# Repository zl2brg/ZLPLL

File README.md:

# ZLPLL
Wayne Knowles ZL2BKC ZLPLL ZLPLL-14G Code. Imported v4.2A from his avrstudio project and added open source licences along with Linux Makefile build support.
v4.4A Fixed floating point precision register calculation inaccuracies by moving to 64/32bit integer math. 
Register calculations are based on Andy G4JNT's code. Frequency calculation now accurate to 10Hz below 6.8Ghz and 20Hz above.

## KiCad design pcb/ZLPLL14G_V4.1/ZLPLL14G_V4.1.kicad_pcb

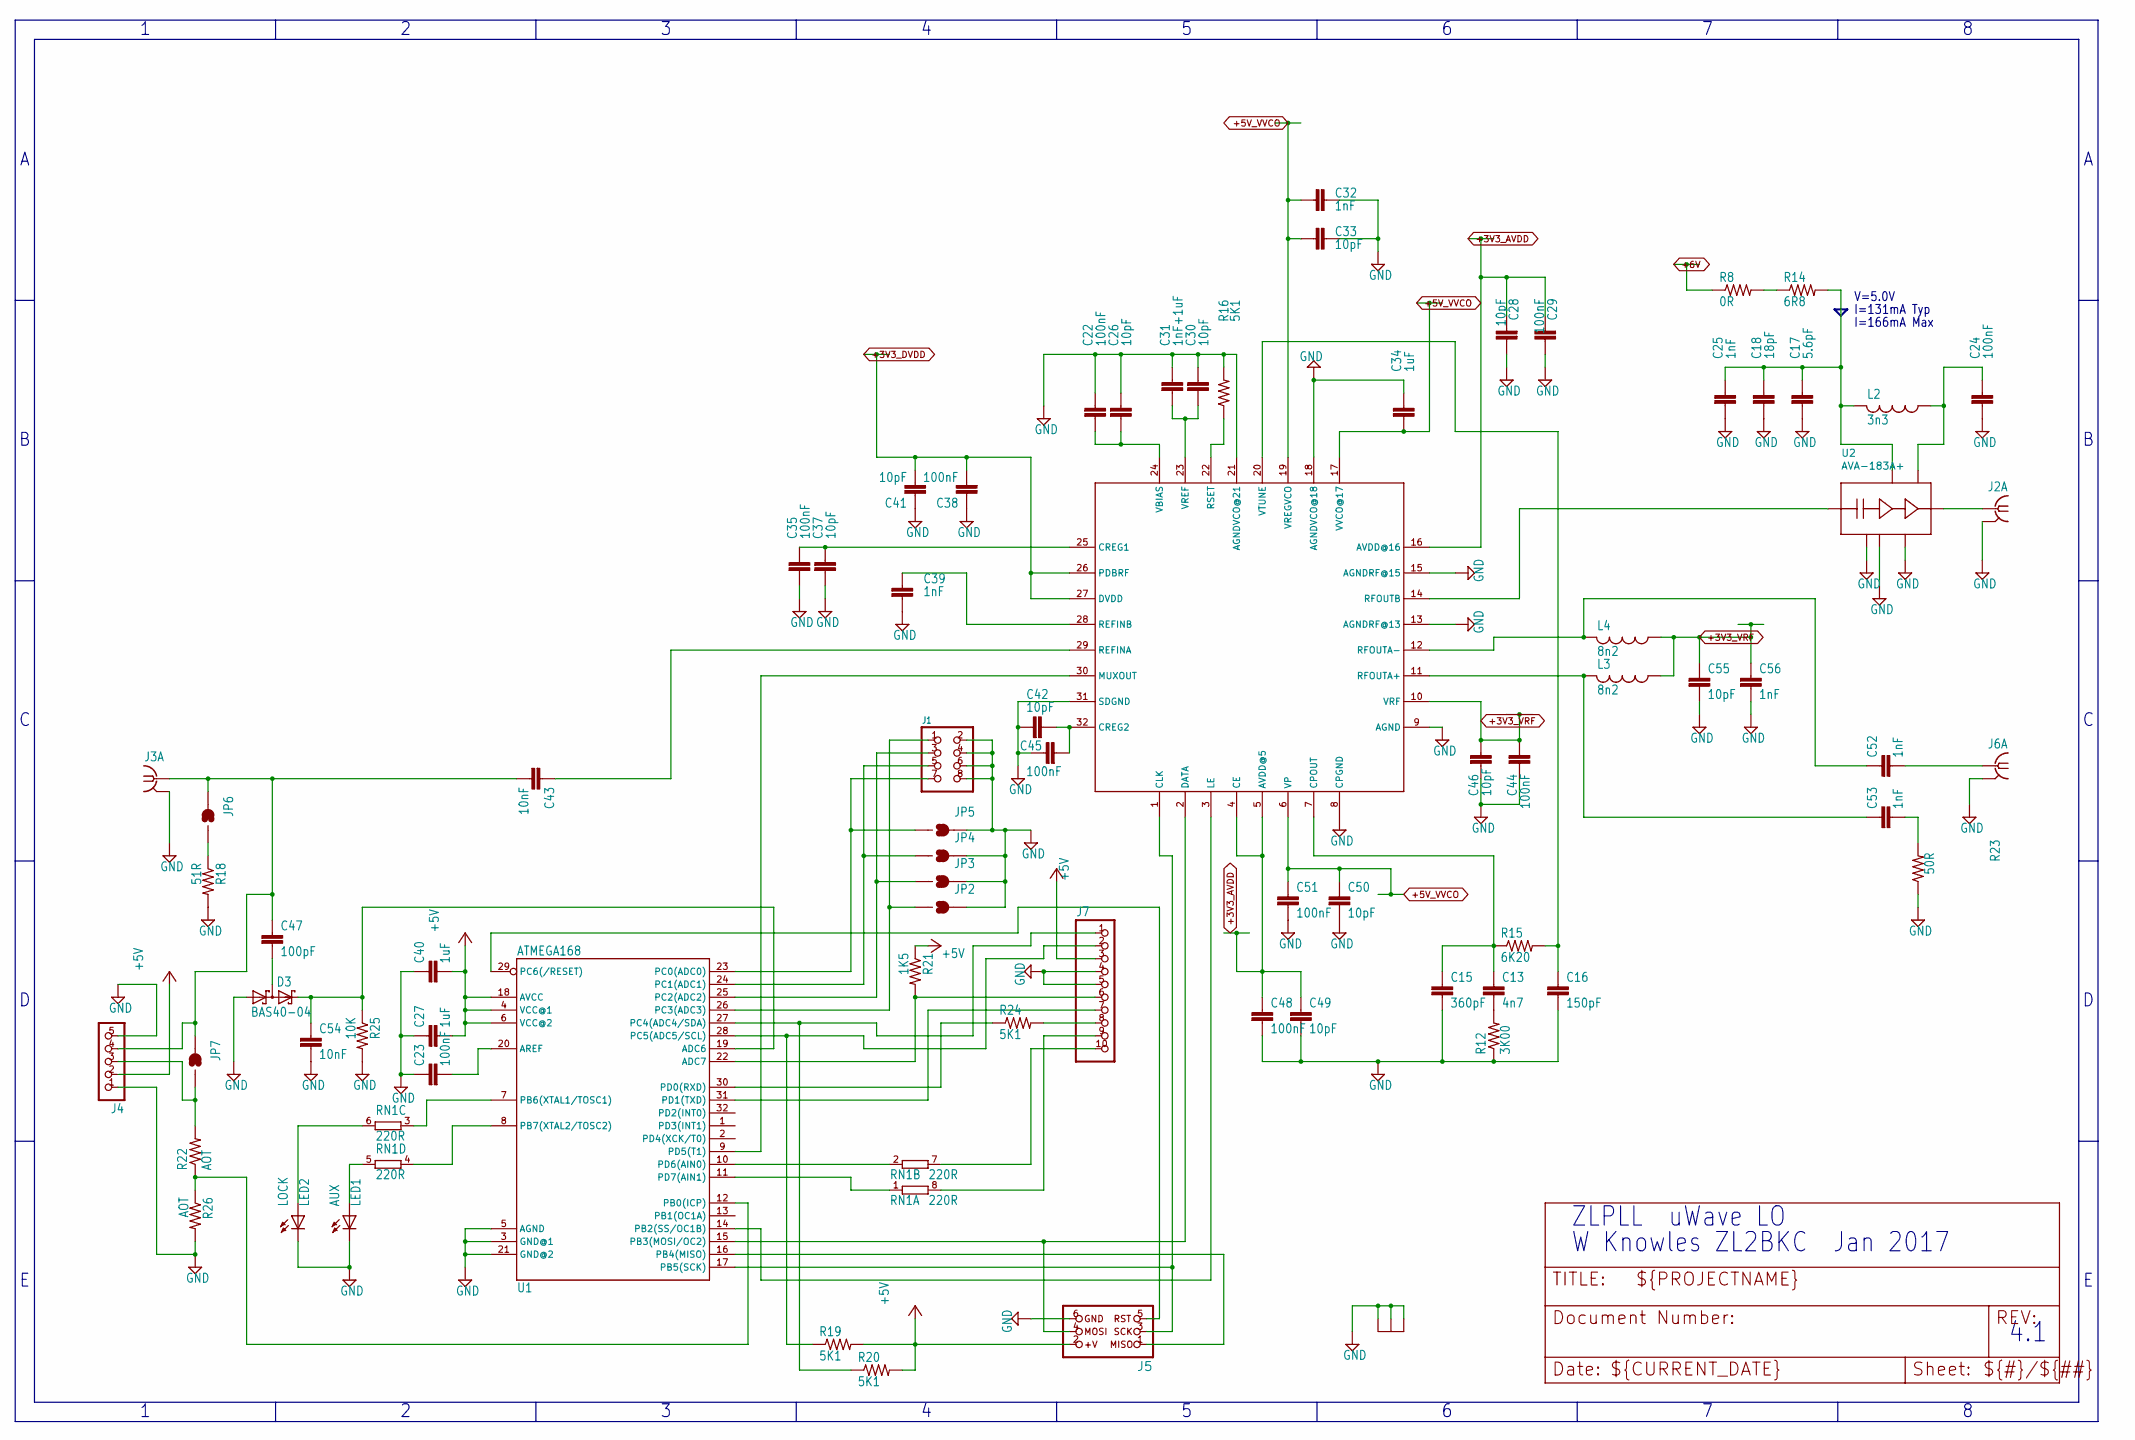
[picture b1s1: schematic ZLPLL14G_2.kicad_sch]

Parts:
C13: 4n7; C0603
C15: 360pF; C0603
C16: 150pF; C0603
C17: 5.6pF; C0402
C18: 18pF; C0402
C22, C24, C29, C35, C38, C44, C45, C48, C51: 100nF; C0402
C23: 100nF; C0603
C25, C32, C39: 1nF; C0402
C26, C28, C30, C33, C37, C41, C42, C46, C49, C50: 10pF; C0402
C27, C40: 1uF; C0603
C31: 1nF+1uF; C0402
C34: 1uF; C0402
C43, C54: 10nF; C0603
C47: 100pF; C0603
C52, C53, C56: 1nF; C0603
C55: 10pF; C0603
D3: BAS40-04; SOT23
J1: CON_HEADER_2X04-PTH; M2X4
J2: SMA-J797
J3, J6: SMA-142-0711-821/826; J502-ND-142-0711-821_826
J4: CON_HEADER_1X05-PTH; M1X5
J5: CON_HEADER_PRG_AVR_ICSP-PTH; HEADER_PRG_2X03
J7: PINHD-1X10; 1X10
JP2, JP3, JP4, JP5, JP7: SOLDERJUMPERNO; SJ_2S-NO
JP6: SOLDERJUMPERNC2; SJ_2S-NOTRACE
L2: 3n3; C0603
L3, L4: 8n2; C0603
LED1: AUX; CHIPLED_0805
LED2: LOCK; CHIPLED_0805
R8: 0R; R1206
R12: 3K00; R0603
R14: 6R8; R1206
R15: 6K20; R0603
R16, R19, R20, R24: 5K1; R0603
R18: 51R; R0603
R21: 1K5; R0603
R22, R26: AOT; R0603
R23: 50R; R0603
R25: 10K; R0603
RN1: 220R; EXBS8V
U1: ATMEGA168; TQFP32-08
U2: AVA-183A+; DQ849
U3: ADF5355; QFN50P500X500X100-33V2N

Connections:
+3V3_AVDD: C28.2, C29.2, C48.1, C49.1, U3.4 (CE), U3.5 (AVDD@5), U3.16 (AVDD@16); also elsewhere on the board
+3V3_DVDD: C38.2, C41.2, U3.26 (PDBRF), U3.27 (DVDD); also elsewhere on the board
+3V3_VRF: C44.1, C46.1, C55.1, C56.1, L3.1, L4.1, U3.10 (VRF); also elsewhere on the board
+5V: C27.2, C40.2, J4.2, J5.2 (+V), J7.3, R19.2, R20.2, R21.1, U1.4 (VCC@1), U1.6 (VCC@2), U1.18 (AVCC); also elsewhere on the board
+5V_VVCO: C32.2, C33.2, C34.2, C50.1, C51.1, U3.6 (VP), U3.17 (VVCO@17), U3.19 (VREGVCO); also elsewhere on the board
+6V: R8.1; also elsewhere on the board
GND: C15.2, C16.2, C17.2, C18.2, C22.1, C23.1, C24.2, C25.2, C26.1, C27.1, C28.1, C29.1, C30.1, C31.1, C32.1, C33.1, C34.1, C35.2, C37.2, C38.1, C39.2, C40.1, C41.1, C42.1, C44.2, C45.1, C46.2, C48.2, C49.2, C50.2, C51.2, C54.2, C55.2, C56.2, D3.1 (A1), J1.2, J1.4, J1.6, J1.8, J2.GND@1 (GND), J2.GND@2 (GND@1), J2.GND@3 (GND@2), J2.GND@4 (GND@3), J2.GND@5 (GND@1), J2.GND@6 (GND@2), J2.GND@7 (GND@3), J3.G@1 (GND), J3.G@2 (GND@1), J3.G@3 (GND@2), J3.G@4 (GND@3), J4.1, J4.5, J5.6 (GND), J6.G@1 (GND), J6.G@2 (GND@1), J6.G@3 (GND@2), J6.G@4 (GND@3), J7.4, J7.5, JP2.2, JP3.2, JP4.2, JP5.2, LED1.C, LED2.C, R12.1, R16.2, R18.2, R23.1, R25.2, R26.2, U1.3 (GND@1), U1.5 (AGND), U1.21 (GND@2), U2.1 (GND@1), U2.6 (GND@2), U2.PAD (GND), U3.8 (CPGND), U3.9 (AGND), U3.13 (AGNDRF@13), U3.15 (AGNDRF@15), U3.18 (AGNDVCO@18), U3.21 (AGNDVCO@21), U3.31 (SDGND), U3.PAD@1_1 (GND@1), U3.PAD@1_2 (GND@2), U3.PAD@1_3 (GND@3), U3.PAD@2_1 (GND@1), U3.PAD@2_2 (GND@2), U3.PAD@2_3 (GND@3), U3.PAD@3_1 (GND@1), U3.PAD@3_2 (GND@2), U3.PAD@3_3 (GND@3); also elsewhere on the board
unnamed: U1.14 (PB2(SS/OC1B)), U3.3 (LE)
unnamed: C23.2, U1.20 (AREF)
unnamed: J5.5 (RST), U1.29 (PC6(/RESET))
unnamed: R16.1, U3.22 (RSET)
unnamed: J7.8, R24.2
unnamed: J7.7, U1.31 (PD1(TXD))
unnamed: R24.1, U1.30 (PD0(RXD))
unnamed: C52.1, L4.2, U3.12 (RFOUTA-)
unnamed: C43.1, U3.29 (REFINA)
unnamed: C47.2, D3.3 (C1A2)
unnamed: C54.1, D3.2 (C2), R25.1, U1.19 (ADC6)
unnamed: C53.1, L3.2, U3.11 (RFOUTA+)
unnamed: J5.4 (MOSI), U1.15 (PB3(MOSI/OC2)), U3.2 (DATA)
unnamed: C13.2, R12.2
unnamed: J2.PIN (1), U2.5 (OUT)
unnamed: C13.1, C15.1, R15.1, U3.7 (CPOUT)
unnamed: U1.9 (PD5(T1)), U3.30 (MUXOUT)
unnamed: RN1.4 (1), U1.8 (PB7(XTAL2/TOSC2))
unnamed: J5.1 (MISO), U1.16 (PB4(MISO))
unnamed: RN1.2 (1), U1.10 (PD6(AIN0))
unnamed: J5.3 (SCK), U1.17 (PB5(SCK)), U3.1 (CLK)
unnamed: C16.1, R15.2, U3.20 (VTUNE)
unnamed: U2.2 (IN), U3.14 (RFOUTB)
unnamed: JP6.1, R18.1
unnamed: C53.2, R23.2
unnamed: J1.7, JP5.1, U1.23 (PC0(ADC0))
unnamed: C24.1, L2.1, U2.8 (DC8)
unnamed: J7.6, R21.2, U1.22 (ADC7)
unnamed: C22.2, C26.2, U3.24 (VBIAS)
unnamed: C30.2, C31.2, U3.23 (VREF)
unnamed: C52.2, J6.1
unnamed: R8.2, R14.1
unnamed: J4.3, JP7.1, R22.2
unnamed: R22.1, R26.1, U1.12 (PB0(ICP))
unnamed: J1.5, JP4.1, U1.24 (PC1(ADC1))
unnamed: J1.3, JP3.1, U1.25 (PC2(ADC2))
unnamed: J1.1, JP2.1, U1.26 (PC3(ADC3))
unnamed: J7.1, R20.1, U1.27 (PC4(ADC4/SDA))
unnamed: J7.2, R19.1, U1.28 (PC5(ADC5/SCL))
unnamed: C43.2, C47.1, J3.1, J4.4, JP6.2, JP7.2
unnamed: RN1.3 (1), U1.7 (PB6(XTAL1/TOSC1))
unnamed: RN1.1, U1.11 (PD7(AIN1))
unnamed: LED1.A, RN1.5 (2)
unnamed: LED2.A, RN1.6 (2)
unnamed: J7.9, RN1.8 (2)
unnamed: J7.10, RN1.7 (2)
unnamed: C17.1, C18.1, C25.1, L2.2, R14.2, U2.7 (DC7)
unnamed: C35.1, C37.1, U3.25 (CREG1)
unnamed: C39.1, U3.28 (REFINB)
unnamed: C42.2, C45.2, U3.32 (CREG2)

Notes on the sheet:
I=166mA Max
V=5.0V
ZLPLL uWave LO
I=131mA Typ
W Knowles ZL2BKC Jan 2017
4.1

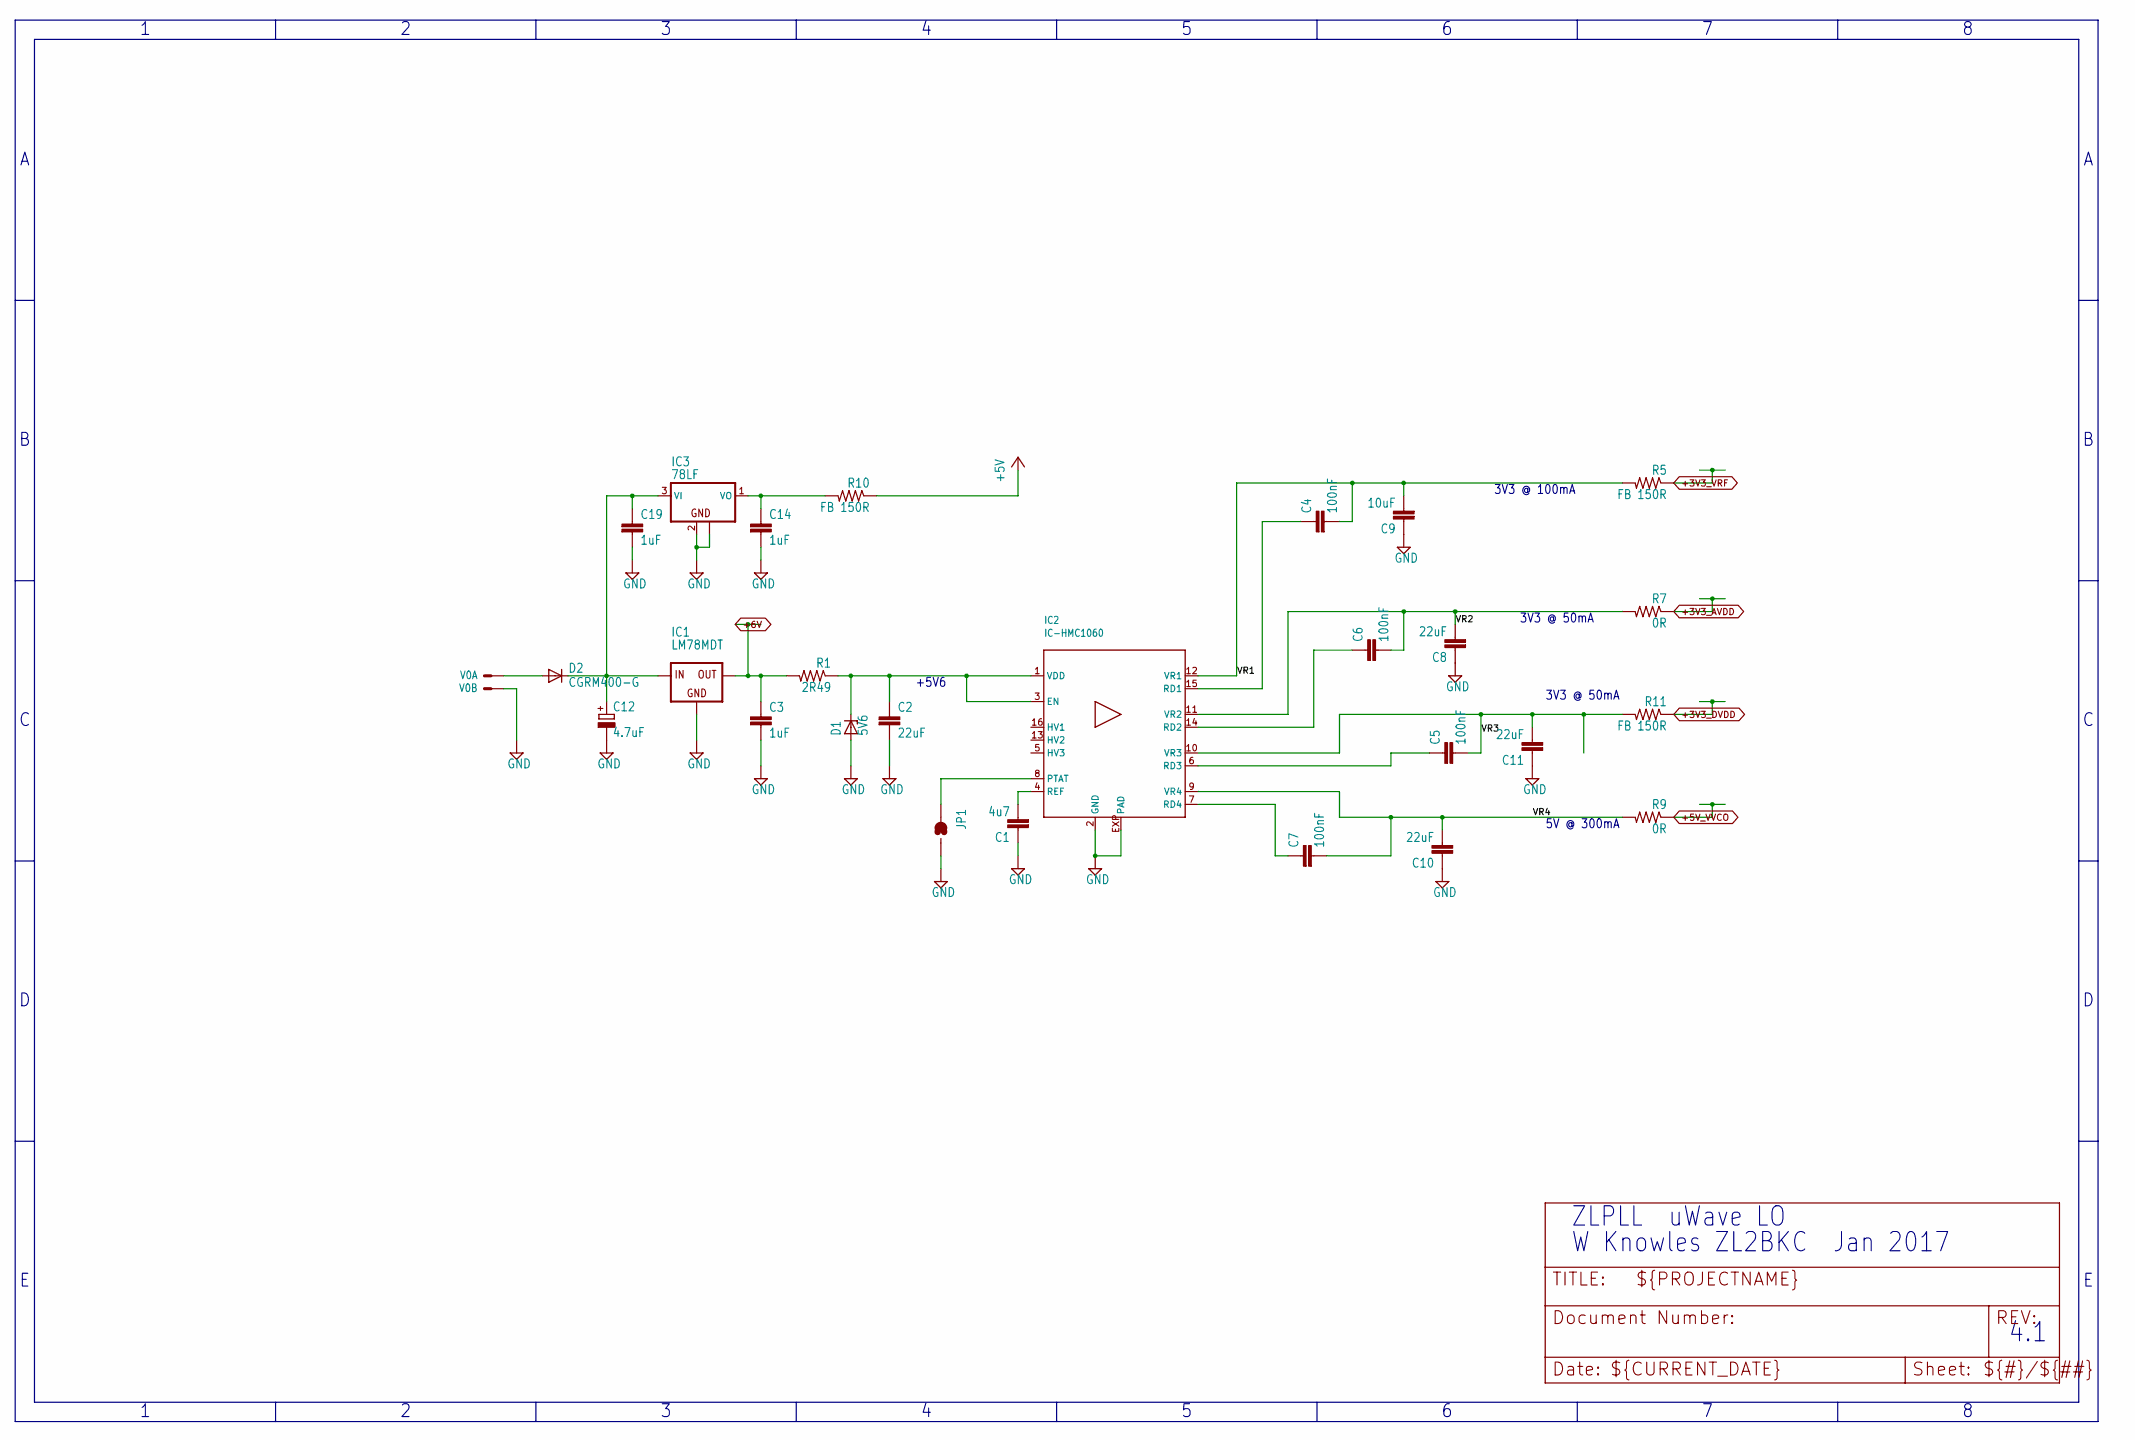
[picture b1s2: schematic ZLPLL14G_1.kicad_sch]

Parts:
C1: 4u7; C0603
C2, C8, C10, C11: 22uF; C0603
C3, C14, C19: 1uF; C0603
C4, C5, C6, C7: 100nF; C0603
C9: 10uF; C0603
C12: 4.7uF; CT3528
D1: 5V6; SOD80C
D2: CGRM400-G; SOD-123_MINI-SMA
IC1: LM78MDT; DPACK
IC2: IC-HMC1060; QFN16
IC3: 78LF; SOT89
JP1: SOLDERJUMPERNO; SJ_2S-NO
R1: 2R49; R1206
R5, R10, R11: FB 150R; R0603
R7, R9: 0R; R0603
V0: 22-23-2021

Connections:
+3V3_AVDD: R7.1; also elsewhere on the board
+3V3_DVDD: R11.1; also elsewhere on the board
+3V3_VRF: R5.1; also elsewhere on the board
+5V: R10.1; also elsewhere on the board
+5V_VVCO: R9.1; also elsewhere on the board
+6V: C3.1, IC1.3 (OUT), R1.2; also elsewhere on the board
GND: C1.1, C2.2, C3.2, C8.1, C9.1, C10.1, C11.1, C12.-, C14.2, C19.2, D1.A, IC1.4 (GND), IC2.2 (GND), IC2.EXP (PAD), IC3.2 (GND), IC3.2@1 (GND@1), JP1.1, V0.2; also elsewhere on the board
unnamed: C2.1, D1.C, IC2.1 (VDD), IC2.3 (EN), R1.1
unnamed: C12.+, C19.1, D2.C, IC1.1 (IN), IC3.3 (VI)
unnamed: C7.1, IC2.7 (RD4)
unnamed: D2.A, V0.1
unnamed: C14.1, IC3.1 (VO), R10.2
unnamed: IC2.8 (PTAT), JP1.2
unnamed: C4.1, IC2.15 (RD1)
unnamed: C6.1, IC2.14 (RD2)
unnamed: C5.1, IC2.6 (RD3)
unnamed: C1.2, IC2.4 (REF)
VR1: C4.2, C9.2, IC2.12 (VR1), R5.2
VR2: C6.2, C8.2, IC2.11 (VR2), R7.2
VR3: C5.2, C11.2, IC2.10 (VR3), R11.2
VR4: C7.2, C10.2, IC2.9 (VR4), R9.2

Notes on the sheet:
3V3 @ 50mA
ZLPLL uWave LO
+5V6
W Knowles ZL2BKC Jan 2017
5V @ 300mA
3V3 @ 100mA
4.1

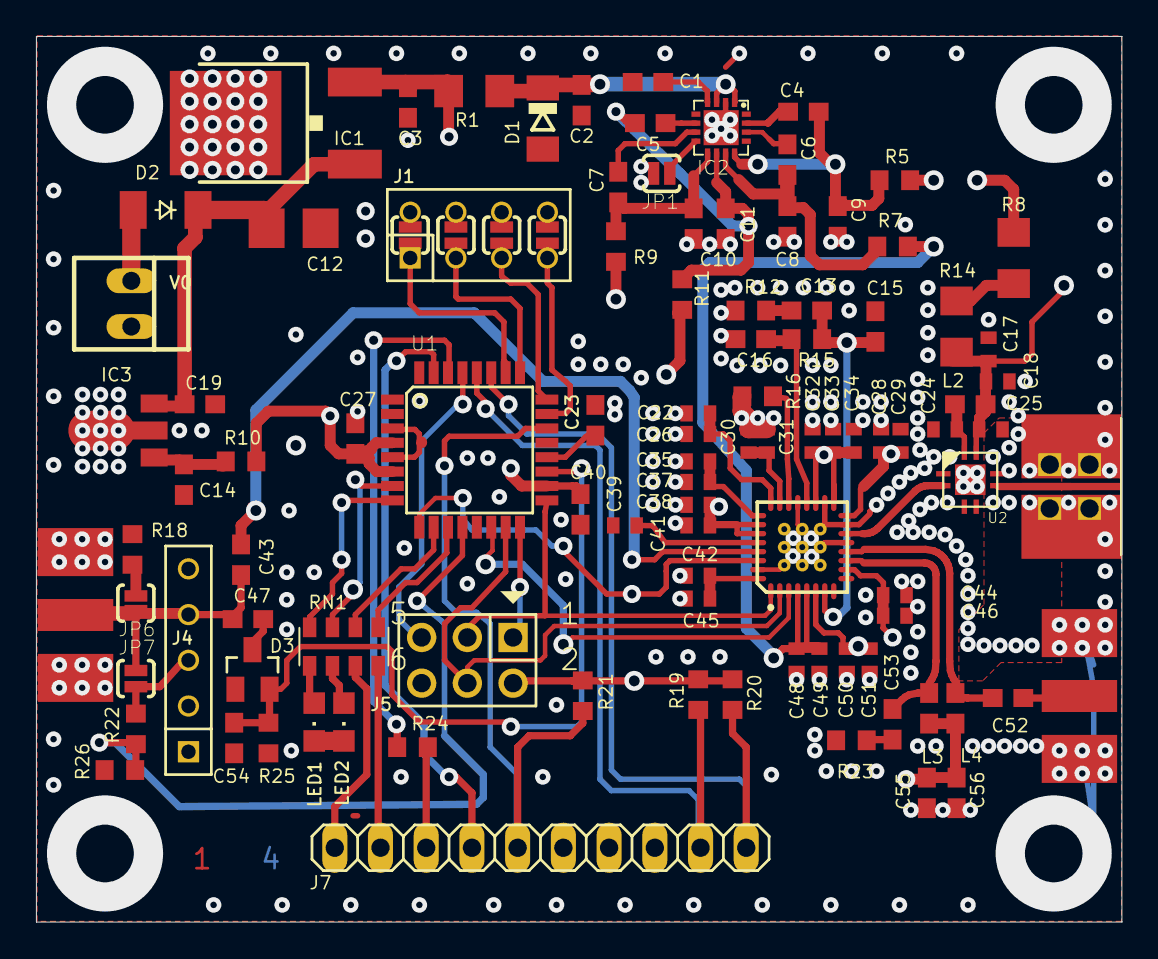
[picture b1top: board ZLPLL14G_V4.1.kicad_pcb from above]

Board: 4 copper layers, 60.3 x 49.2 mm, 103 parts (0 on the bottom side), 71 nets.

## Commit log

2023-08-10 Imported Wayne Knowles ZL2BKC's v4.2a ZLPLL source code from avrsudio and added Makefile and added gpl licences as required
2024-01-04 First commit of ZL2BKC v3 ADF4350 source code
2024-01-04 First commit of ZL2BKC v3,x ADF4350 ZLPLL source code
2024-01-04 Misc cleanup
2024-01-05 Added misc pre compiled binaries and documentation
2024-01-24 Added pcb schmatics and board prints
2024-02-08 Added v4.1 kicad pcb
2024-04-07 Added V3.1B pcb
2025-04-03 V4.4A Fixed frequency calculation issues by moving register calculation to fixed integer math
2025-04-03 Update README.md
    Updated for V4.4A
2025-04-03 Added range checking for ref frequency
2025-04-03 Added ZLPLL.4.4A.hex
2025-08-28 Initial plan
2025-12-02 Rev 4.4B Fixed reg6 divisor error, improved freq parsing
